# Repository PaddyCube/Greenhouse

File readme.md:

# smartGreenhouse, an Greenhouse monitoring and control system based on ESP32
smartGreenhouse is a monitoring and control system for your Greenhouse. It uses an ESP32 DEVKIT V1 module as main MCU. 
As my greenhouse is a small one, the commonly used window lift (wax filled zylinder) didn't fit. So I build a linear actuator to move window.
Also I wanted to measure and collect environmental data.

Disclaimer: this project runs great for me. But I'm not responsible for any damage or harm of people. It comes without any warranty !!!
## Functions
With smartGreenhouse you can
- measure temperature
- measure humidity
- monitor door state (open/closed)
- monitor window states (open/closed)
- control up to 5 outputs for
	- heater
	- water
	- fan
	- light
	- other
- control motorized windows
- measure battery and solar voltage
- send data via mqtt to your broker
- send commands to greenhouse from your broker

It also provides:
- LCD display to visualize data 
- wifi configuration interface
- simple switch to control light, water and wifi hotspot
- PCB schematics and files (KICAD)

## Operational state
smartGreenhouse has two main states, which are AUTOMATIC and MANUAL. While in AUTOMATIC mode, it will take care of everything for you. When in MANUAL,
you can control outputs and window positions like you want. smartGreenhouse will enter AUTOMATIC mode again after some time (MANUAL_TIMEOUT, see below)

If any error occurs, it es to error state. This state can only , if you either reset the device (boot), of by MQTT command. Possible errors are:
- no data from BME280
- window endstop errors (open and close endstop triggered at the same time) 

If in error state, all outputs will be turned off (no heater, no fan etc.). Also windows can't be operated.

## Environmental data
To measure environmental data like temperature and humidity, a BME280 sensor gets used. It is connected to I2C port of ESP32 module

## door and window states
Depending on your needs, you can check, if doors and windows are opened or closed. These endstops can be simple reed contacts or switches. For security reasons,
please use normally-closed (NC) contacts for windows. This ensures safe operation, even if your cable is broken or has only poor contact. For door, it doesn't matter
as the door is not motorized (yet).

## Output
A four-channel relais module gets used to switch different outputs like turning on/off heater or water. For light, I use a FR120N MOSFET module, but relais will work here
as well. Thanks to relais, you can also switch high voltage like 230V for a heater. Or you use battery power, like 12V for a fan. It is up to you to hook up what you need.

ATTENTION: 230V IS DANGEROUS. ONLY USE IT, IF YOU KNOW WHAT YOU DO. DON'T BLAME ME, IF YOU KILLED YOURSELF

### Heater
Heaters can be turned on/off automatically based on temperature. You can specify  min and max temperature for heater. If actual temp is below min_temp,
heaters will be turned on. If temp raises above max_temp, heater will be turned off.

### Fan
Fan gets turned on/off based on humidity. If humidity is above a given value (see configuration), fan gets turned on. If it is below this threshold, fan gets turned off.

### Water
Water can only be controlled manually, either by double press on the button, or by sending a command via mqtt.
If water gets turned on, it will run as long as water_timeout has not been reached (see configuration). You can turn it off before, if you double press the button
again or send a command via mqtt.

### Other
This is an additional output without any special purpose. You can use it for whatever you want. It is also possible to combine this output with other meaning
this output gets toggled together with lights and motors. I need this as my battery is a 12V one and motors and light need 24V. I use a DC/DC step up converter,
which only gets enabled, if light and motor are in use.

### Light
With light, I don't mean these plant lights to grow your stuff. I mean a simple light so you'll find vegetables even at night :-)
Light gets either turned on/off by single press of button, or by mqtt command. It will be turned on as long as light_timeout didn't get reached. You can
also press he switch again or send a mqtt command, to turn off before timeout has been reached.

## Window operation
with smartGreenhouse, you can control up to two motorized windows, which gets operated simultaneously. Each window as to be equipped with upper and lower endstops.
smartGreenhouse monitors these endstops individually for each window. So if one window closes faster, it stops when reaching it's endstop while the other window continues 
to close.

A few parameters are taken into account to operate window. For details, see Configuration section below.
- min temperature: if temp is below this value, windows gets fully closed
- max temperature: whem temp is above this value, windows gets fully opened
- positions: how many stops between min and max temp
- step time: duration in seconds motor must run to reach next window positions. Needed as we don't have feedback sensors of actual positions

### Operation mode
When temp is above min_temperature, a window position gets calculated based on difference between actual temperature and min temperature.
Example:
- min_temp 18 C°
- actual_temp 20 C°
- max_temp (fully open) 24 C°
- positions: 6

Window should start to open at 18C° and should be fully opened at 24C°. Between this, 6 different stop positions are allowed. 
Window target position = actual_temp - min_temp / ( [max_temp - min_temp] / positions ) = 2

Motor will be controlled to reach position 2 (operate for 2x step_time).

Beside window position, endstops will be taken into account in any case. If one gets reached, it will always stop and reset position.

## Battery and Solar
I use a 12V lead-acid battery in conjunction with a solar charge controller to run smartGreenhouse. It is not mandatory to run it off battery with solar.
You can also operate it from a simple USB 5V mobile phone charger, if you want.
If you use battery and solar, you can measure battery voltage as well as solar voltage.

## send data to MQTT broker
smartGreenhouse sends every x seconds a message to your mqtt broker. It is up to you to use or not use these data. I use node-red to visualize.

## receive commands from MQTT broker
you can send commands to turn on/off any output and also to operate windows manually. Before that, you need to change operation state from AUTO to MANUAL,
also by command. For details, see Command section below.

## LCD Display
I use a 2004 LCD display attached by I2C to visualize enviromental and operational data. This way, you can check data when you're inside the greenhouse
but without using your phone.

## Wifi configuration interface
during boot and after a long-press of the button, ESP32 will create a wifi access point. By connecting to this with your phone or PC, you can set up wifi connection
to your home wifi as well as set different parameters. 

- first connect to the WIFI AP of smartGreenhouse. If none gets shown, either restart or long-press button.
- after connected, enter the following address in your browser: http://192.168.4.1 to open configuration wizard.

## PCB Schematics
Beside the code for your ESP32 DevKit V1, this repository also comes with a KiCAD project for a PCB board.

# Your own build
## BOM
- ESP32 DevKit V1 (36 pin version)
- BME280
- 4-channel relais board
- FR120N Mosfet Module or 1-channel relais board
- L298N motor controller
- 2004 LCD display with I2C interface
- push button 
- some resistors, contact terminals, jumpers

## Configuration
### CONFIG.H
Have a look at CONFIG.H, which defines some fixed values. Most of the parameters should be self-explanatory. Here you find MQTT send interval and MQTT topic names.
Also you define how many windows you want to control, if dorr should be monitored and so on. CHECK THIS FILE

### WIFI configuration
After connect to smartGreenhouse's WIFI AP, you can set the following parameters:
- MQTT Server: address of your mqtt broker
- MQTT port: port number of your mqtt broker
- wait, what about MQTT security? Sorry, not implemented so far

- Num of window positions: number of stops between fully closed and fully opened window
- close window if temp below C°: if temp is lower, window will be closed (and keep closed)
- fully open window if temp above C°: if temp is above this value, windows will be opened to its maximum.
- time(s) position: how many seconds must the motor run, to reach next position

- turn heater on, if temp below C°
- turn heater off, if temp above C°

- turn fan on, if humidity is above %

- run water pump for (s): when water pump gets enabled, how long should it keeped on before turning water pump off?
- Timeout for light (s): when light has been turned on, turn it off after this time.

## MQTT commands
### toggle auto / manual state
To switch to AUTOMATIC mode, use this command
```
{"command":"setMode","parameter":"AUTO"}
```

To switch to MANUAL state, use this command
```
{"command":"setMode","parameter":"MANUAL"}
```

### reset error state

### move window
To move the windows to a given position, use this command. Please note, it only works, if you switch operation mode to MANUAL_TIMEOUT
```
{"command":"WINDOW","parameter":"<your position>"}
```

### toggle outputs
To toggle any output, use one of the commands below

```
{"command":"RELAIS_ON","parameter":"HEATER"}
{"command":"RELAIS_OFF","parameter":"HEATER"}
{"command":"RELAIS_ON","parameter":"FAN"}
{"command":"RELAIS_OFF","parameter":"FAN"}
{"command":"RELAIS_ON","parameter":"WATER"}
{"command":"RELAIS_OFF","parameter":"WATER"}
{"command":"RELAIS_ON","parameter":"OTHERS"}
{"command":"RELAIS_OFF","parameter":"OTHERS"}
{"command":"RELAIS_ON","parameter":"LIGHT"}
{"command":"RELAIS_OFF","parameter":"LIGHT"}
```

# My build
## Pictures of PCB and assembled smartGreenhouse
PCB front and back view

Ugly wiring, you'll do it better

3D printed case. Left smartGreenhouse control unit. Right solar charger and battery. Below switchable 230V plugs

Node-Red user interface

DIY linear actuator to operate windows

40mm Aluminium square pipe, 30mm Aluminium square pipe, M8 lead scred, some nuts and bolts, endswitch and 24V geared motor. Together with 3D printing
you'll get your own linear actuator. To be fair, it is cheaper to buy them. But I had all parts laying around.

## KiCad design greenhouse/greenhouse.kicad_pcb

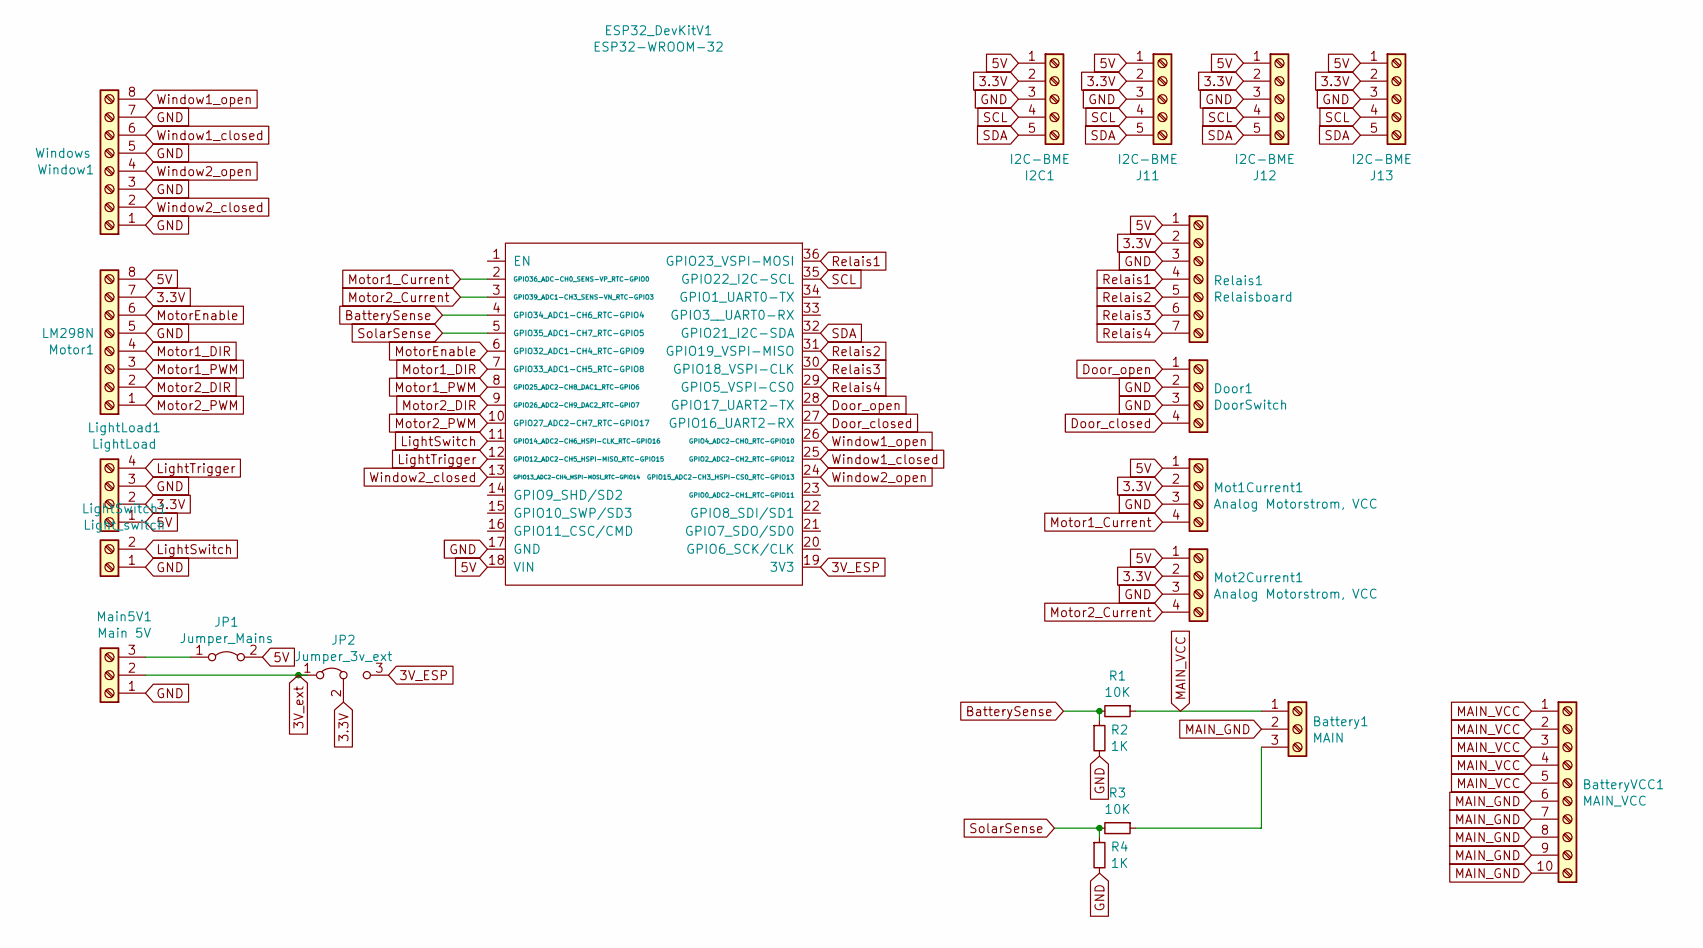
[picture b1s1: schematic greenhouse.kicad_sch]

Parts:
Battery1: MAIN; TerminalBlock_bornier-3_P5.08mm
BatteryVCC1: MAIN_VCC; TerminalBlock_RND_205-00240_1x10_P5.08mm_Horizontal
Door1: DoorSwitch; JST_XH_B4B-XH-A_1x04_P2.50mm_Vertical
ESP32_DevKitV1: ESP32-WROOM-32; ESP32-DOIT-DEVKIT
I2C1: I2C-BME; JST_XH_B5B-XH-A_1x05_P2.50mm_Vertical
J11, J12, J13: I2C-BME; JST_XH_B5B-XH-A_1x05_P2.50mm_Vertical
JP1: Jumper_Mains; PinSocket_1x02_P2.54mm_Vertical
JP2: Jumper_3v_ext; PinSocket_1x03_P2.54mm_Vertical
LightLoad1: LightLoad; JST_XH_B4B-XH-A_1x04_P2.50mm_Vertical
LightSwitch1: Light_switch; JST_XH_B2B-XH-A_1x02_P2.50mm_Vertical
Main5V1: Main 5V; JST_XH_B3B-XH-A_1x03_P2.50mm_Vertical
Mot1Current1, Mot2Current1: Analog Motorstrom, VCC; JST_XH_B4B-XH-A_1x04_P2.50mm_Vertical
Motor1: LM298N; JST_XH_B8B-XH-A_1x08_P2.50mm_Vertical
R1, R3: 10K; R_Axial_DIN0204_L3.6mm_D1.6mm_P7.62mm_Horizontal
R2, R4: 1K; R_Axial_DIN0204_L3.6mm_D1.6mm_P7.62mm_Horizontal
Relais1: Relaisboard; JST_XH_B7B-XH-A_1x07_P2.50mm_Vertical
Window1: Windows; JST_XH_B8B-XH-A_1x08_P2.50mm_Vertical

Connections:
3.3V: I2C1.2, J11.2, J12.2, J13.2, JP2.2 (C), LightLoad1.2, Mot1Current1.2, Mot2Current1.2, Motor1.7, Relais1.2
3V_ESP: ESP32_DevKitV1.19 (3V3), JP2.3 (B)
3V_ext: JP2.1 (A), Main5V1.2
5V: ESP32_DevKitV1.18 (VIN), I2C1.1, J11.1, J12.1, J13.1, JP1.2 (B), LightLoad1.1, Mot1Current1.1, Mot2Current1.1, Motor1.8, Relais1.1
BatterySense: ESP32_DevKitV1.4 (GPIO34_ADC1-CH6_RTC-GPIO4), R1.2, R2.1
Door_closed: Door1.4, ESP32_DevKitV1.27 (GPIO16_UART2-RX)
Door_open: Door1.1, ESP32_DevKitV1.28 (GPIO17_UART2-TX)
GND: Door1.2, Door1.3, ESP32_DevKitV1.17 (GND), I2C1.3, J11.3, J12.3, J13.3, LightLoad1.3, LightSwitch1.1, Main5V1.1, Mot1Current1.3, Mot2Current1.3, Motor1.5, R2.2, R4.2, Relais1.3, Window1.1, Window1.3, Window1.5, Window1.7
LightSwitch: ESP32_DevKitV1.11 (GPIO14_ADC2-CH6_HSPI-CLK_RTC-GPIO16), LightSwitch1.2
LightTrigger: ESP32_DevKitV1.12 (GPIO12_ADC2-CH5_HSPI-MISO_RTC-GPIO15), LightLoad1.4
MAIN_GND: Battery1.2, BatteryVCC1.6, BatteryVCC1.7, BatteryVCC1.8, BatteryVCC1.9, BatteryVCC1.10
MAIN_VCC: Battery1.1, BatteryVCC1.1, BatteryVCC1.2, BatteryVCC1.3, BatteryVCC1.4, BatteryVCC1.5, R1.1
Motor1_Current: ESP32_DevKitV1.2 (GPIO36_ADC-CH0_SENS-VP_RTC-GPIO0), Mot1Current1.4
Motor1_DIR: ESP32_DevKitV1.7 (GPIO33_ADC1-CH5_RTC-GPIO8), Motor1.4
Motor1_PWM: ESP32_DevKitV1.8 (GPIO25_ADC2-CH8_DAC1_RTC-GPIO6), Motor1.3
Motor2_Current: ESP32_DevKitV1.3 (GPIO39_ADC1-CH3_SENS-VN_RTC-GPIO3), Mot2Current1.4
Motor2_DIR: ESP32_DevKitV1.9 (GPIO26_ADC2-CH9_DAC2_RTC-GPIO7), Motor1.2
Motor2_PWM: ESP32_DevKitV1.10 (GPIO27_ADC2-CH7_RTC-GPIO17), Motor1.1
MotorEnable: ESP32_DevKitV1.6 (GPIO32_ADC1-CH4_RTC-GPIO9), Motor1.6
unnamed: Battery1.3, R3.1
unnamed: JP1.1 (A), Main5V1.3
Relais1: ESP32_DevKitV1.36 (GPIO23_VSPI-MOSI), Relais1.4
Relais2: ESP32_DevKitV1.31 (GPIO19_VSPI-MISO), Relais1.5
Relais3: ESP32_DevKitV1.30 (GPIO18_VSPI-CLK), Relais1.6
Relais4: ESP32_DevKitV1.29 (GPIO5_VSPI-CS0), Relais1.7
SCL: ESP32_DevKitV1.35 (GPIO22_I2C-SCL), I2C1.4, J11.4, J12.4, J13.4
SDA: ESP32_DevKitV1.32 (GPIO21_I2C-SDA), I2C1.5, J11.5, J12.5, J13.5
SolarSense: ESP32_DevKitV1.5 (GPIO35_ADC1-CH7_RTC-GPIO5), R3.2, R4.1
Window1_closed: ESP32_DevKitV1.25 (GPIO2_ADC2-CH2_RTC-GPIO12), Window1.6
Window1_open: ESP32_DevKitV1.26 (GPIO4_ADC2-CH0_RTC-GPIO10), Window1.8
Window2_closed: ESP32_DevKitV1.13 (GPIO13_ADC2-CH4_HSPI-MOSI_RTC-GPIO14), Window1.2
Window2_open: ESP32_DevKitV1.24 (GPIO15_ADC2-CH3_HSPI-CS0_RTC-GPIO13), Window1.4

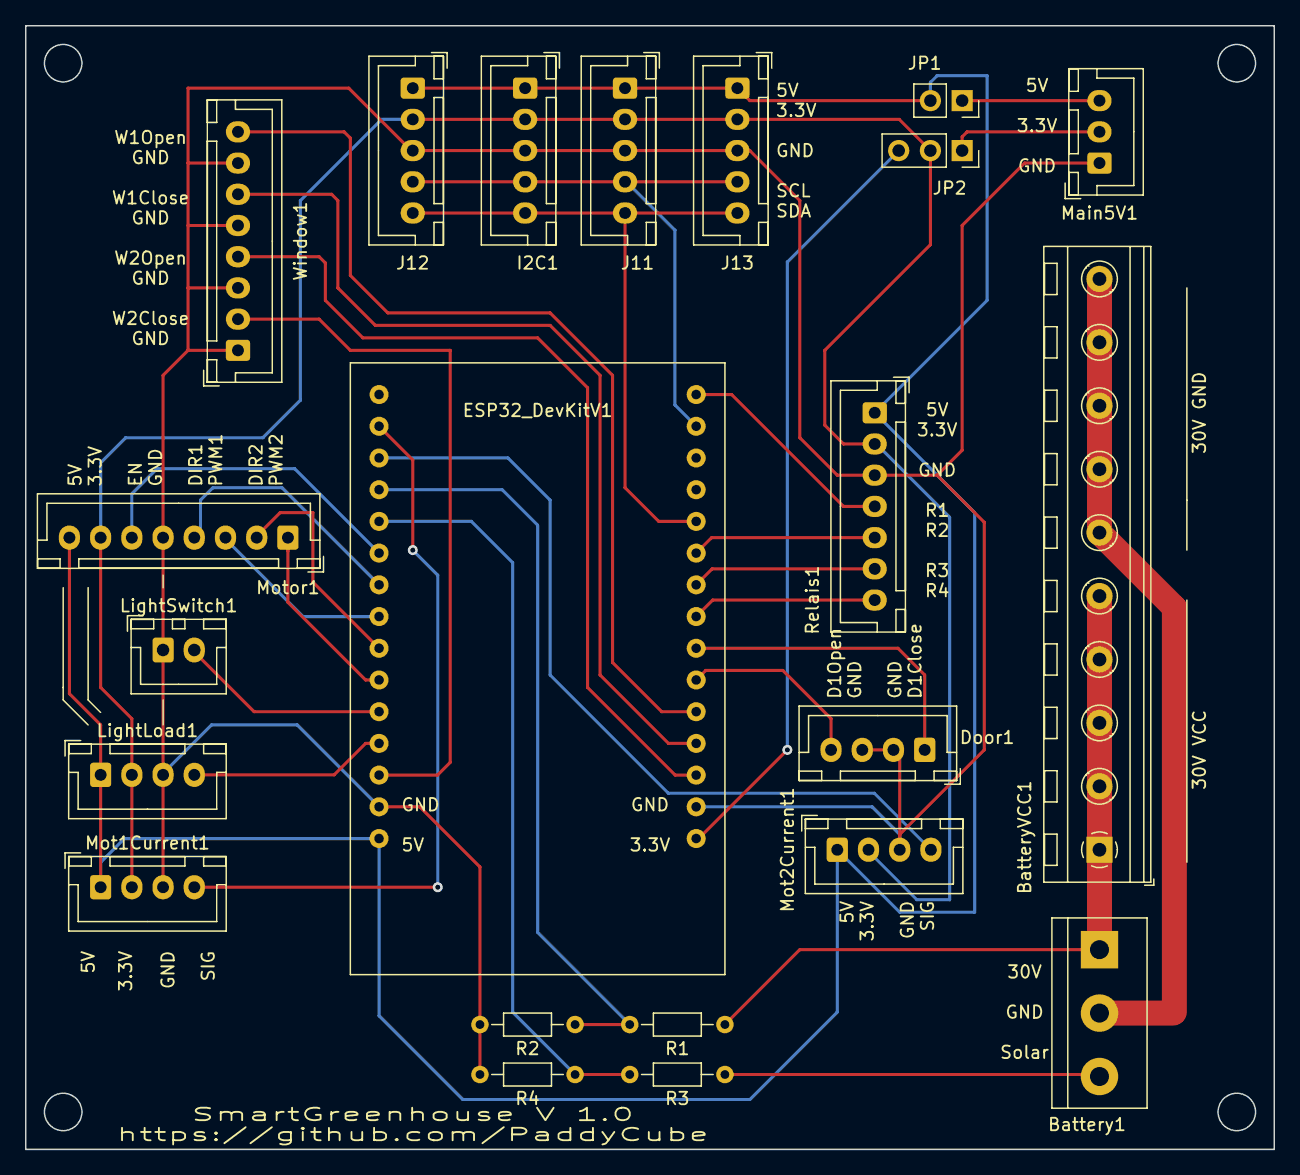
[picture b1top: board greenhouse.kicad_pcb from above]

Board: 2 copper layers, 100.0 x 90.0 mm, 22 parts (0 on the bottom side), 32 nets.

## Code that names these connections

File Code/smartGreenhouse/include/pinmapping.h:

#ifndef _PINMAPPING_H
#define _PINMAPPPING_H
/*
This file defines the pins.
DON'T CHANGE THEM IF YOU DON'T KNOW WHAT YOU DO

*/
// limit switches of windows and doors
#define pin_window1_closed 2
#define pin_window1_open 4
#define pin_window2_closed 13
#define pin_window2_open 15
#define pin_door_open 16
#define pin_door_closed 17

// motor driver control pins
#define pin_motor1_in1 33
#define pin_motor1_in2 25
#define pin_motor2_in1 27
#define pin_motor2_in2 26
#define pin_motor_enable 32 // enables motor driver
#define pin_motor1_current 36 // motor 1 current sense VP
#define pin_motor2_current 39 // motor 2 current sense VN

// voltage measurement
#define pin_vcc_solar 35
#define pin_vcc_battery 34	
			
// light and switch            
#define pin_light_switch 14 // switch for user input
#define pin_light_load 12 // relais to control light

// other loads like fans, water pumps, heaters	
#define pin_relais1 23 // heater
#define pin_relais2 19 // fan
#define pin_relais3 18 // water pump
#define pin_relais4	5


#endif

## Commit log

2023-01-20 rework of PCB
2023-02-08 add BME280 sensor
2023-02-10 Button added
2023-03-05 functional test approved
2023-03-10 default mqtt send interval
2023-03-17 Update readme.md
    typo
2023-03-24 fix window endstop
2023-03-24 small fixes
2023-04-05 debounce window endstops
2023-04-19 more window settings
2023-06-28 minor hotfixes
